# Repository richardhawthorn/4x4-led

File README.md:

### Features

- ESP8266 wifi processor
- 16 RGB Neopixels
- 2 x button inputs
- 3.3V operation
- Mini USB power connector
- FTDI programming port

### License

This work is licensed under a Creative Commons Attribution-ShareAlike 4.0 International License.

<br />
Designed by <a xmlns:cc="http://creativecommons.org/ns#" href="http://www.richardhawthorn.com" property="cc:attributionName" rel="cc:attributionURL" target="_blank">Richard Hawthorn</a><br />
<a rel="license" href="http://creativecommons.org/licenses/by-sa/4.0/" target="_blank">View License</a>

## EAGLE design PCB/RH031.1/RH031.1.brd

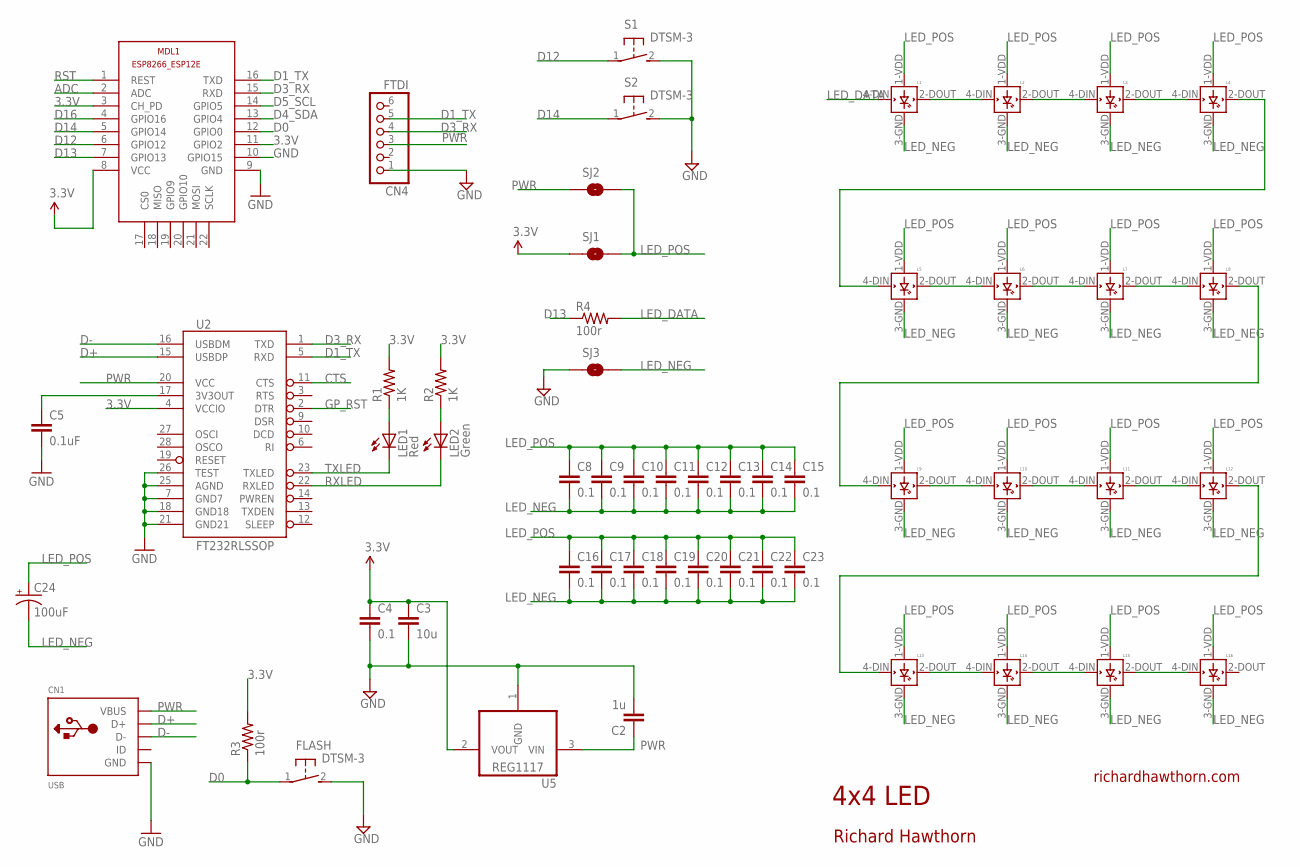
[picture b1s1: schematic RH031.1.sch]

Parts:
C2: 1u; 0603-CAP
C3: 10u; 0805-CAP
C4, C8, C9, C10, C11, C12, C13, C14, C15, C16, C17, C18, C19, C20, C21, C22, C23: 0.1; 0603-CAP
C5: 0.1uF; 0805
C24: 100uF; EIA7343
CN1: USB; USB-MINIB
CN4: FTDI; 1X06
FLASH: DTSM-3
L1, L2, L3, L4, L5, L6, L7, L8, L9, L10, L11, L12, L13, L14, L15, L16: WS2812B
LED1: Red; CHIPLED_0805
LED2: Green; CHIPLED_0805
MDL1: ESP8266-12EESP8266-ESP12E; ESP8266-ESP12E
R1, R2: 1K; 0805
R3, R4: 100r; 0603-RES
S1, S2: DTSM-3
SJ1, SJ2, SJ3: SOLDERJUMPERNO; SJ_2S-NO
U2: FT232RLSSOP; SSOP28DB
U5: REG1117; SOT223

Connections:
3.3V: C3.1, C4.1, MDL1.3 (CH_PD), MDL1.8 (VCC), MDL1.11 (GPIO2), R1.2, R2.2, R3.2, SJ1.1, U2.4 (VCCIO), U5.2 (VOUT)
3.3VOUT: C5.1, U2.17 (3V3OUT)
ADC: MDL1.2 (ADC)
CTS: U2.11 (CTS)
D0: FLASH.1, MDL1.12 (GPIO0), R3.1
D1_TX: CN4.5, MDL1.16 (TXD), U2.5 (RXD)
D3_RX: CN4.4, MDL1.15 (RXD), U2.1 (TXD)
D4_SDA: MDL1.13 (GPIO4)
D5_SCL: MDL1.14 (GPIO5)
D12: MDL1.6 (GPIO12), S1.1
D13: MDL1.7 (GPIO13), R4.1
D14: MDL1.5 (GPIO14), S2.1
D16: MDL1.4 (GPIO16)
D+: CN1.D+, U2.15 (USBDP)
D-: CN1.D-, U2.16 (USBDM)
GND: C2.2, C3.2, C4.2, C5.2, CN1.GND, CN4.1, FLASH.2, MDL1.9 (GND), MDL1.10 (GPIO15), S1.2, S2.2, SJ3.1, U2.7 (GND7), U2.18 (GND18), U2.21 (GND21), U2.25 (AGND), U2.26 (TEST), U5.1 (GND)
GP_RST: U2.2 (DTR)
LED-MID-1: L5.2-DOUT (DOUT), L6.4-DIN (DIN)
LED-MID-2: L7.2-DOUT (DOUT), L8.4-DIN (DIN)
LED-MID-3: L9.2-DOUT (DOUT), L10.4-DIN (DIN)
LED-OUT-1: L1.2-DOUT (DOUT), L2.4-DIN (DIN)
LED-OUT-2: L3.2-DOUT (DOUT), L4.4-DIN (DIN)
LED-OUT-3: L4.2-DOUT (DOUT), L5.4-DIN (DIN)
LED-OUT-4: L12.2-DOUT (DOUT), L13.4-DIN (DIN)
LED-OUT-5: L13.2-DOUT (DOUT), L14.4-DIN (DIN)
LED-OUT-6: L15.2-DOUT (DOUT), L16.4-DIN (DIN)
LED_DATA: L1.4-DIN (DIN), R4.2
LED_NEG: C8.2, C9.2, C10.2, C11.2, C12.2, C13.2, C14.2, C15.2, C16.2, C17.2, C18.2, C19.2, C20.2, C21.2, C22.2, C23.2, C24.C (-), L1.3-GND (GND), L2.3-GND (GND), L3.3-GND (GND), L4.3-GND (GND), L5.3-GND (GND), L6.3-GND (GND), L7.3-GND (GND), L8.3-GND (GND), L9.3-GND (GND), L10.3-GND (GND), L11.3-GND (GND), L12.3-GND (GND), L13.3-GND (GND), L14.3-GND (GND), L15.3-GND (GND), L16.3-GND (GND), SJ3.2
LED_POS: C8.1, C9.1, C10.1, C11.1, C12.1, C13.1, C14.1, C15.1, C16.1, C17.1, C18.1, C19.1, C20.1, C21.1, C22.1, C23.1, C24.A (+), L1.1-VDD (VDD), L2.1-VDD (VDD), L3.1-VDD (VDD), L4.1-VDD (VDD), L5.1-VDD (VDD), L6.1-VDD (VDD), L7.1-VDD (VDD), L8.1-VDD (VDD), L9.1-VDD (VDD), L10.1-VDD (VDD), L11.1-VDD (VDD), L12.1-VDD (VDD), L13.1-VDD (VDD), L14.1-VDD (VDD), L15.1-VDD (VDD), L16.1-VDD (VDD), SJ1.2, SJ2.2
unnamed: LED1.A, R1.1
unnamed: LED2.A, R2.1
unnamed: L2.2-DOUT (DOUT), L3.4-DIN (DIN)
unnamed: L6.2-DOUT (DOUT), L7.4-DIN (DIN)
unnamed: L8.2-DOUT (DOUT), L9.4-DIN (DIN)
unnamed: L10.2-DOUT (DOUT), L11.4-DIN (DIN)
unnamed: L11.2-DOUT (DOUT), L12.4-DIN (DIN)
unnamed: L14.2-DOUT (DOUT), L15.4-DIN (DIN)
PWR: C2.1, CN1.VBUS, CN4.3, SJ2.1, U2.20 (VCC), U5.3 (VIN)
RST: MDL1.1 (REST)
RXLED: LED2.C, U2.22 (RXLED)
TXLED: LED1.C, U2.23 (TXLED)

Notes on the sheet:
4x4 LED
richardhawthorn.com
Richard Hawthorn

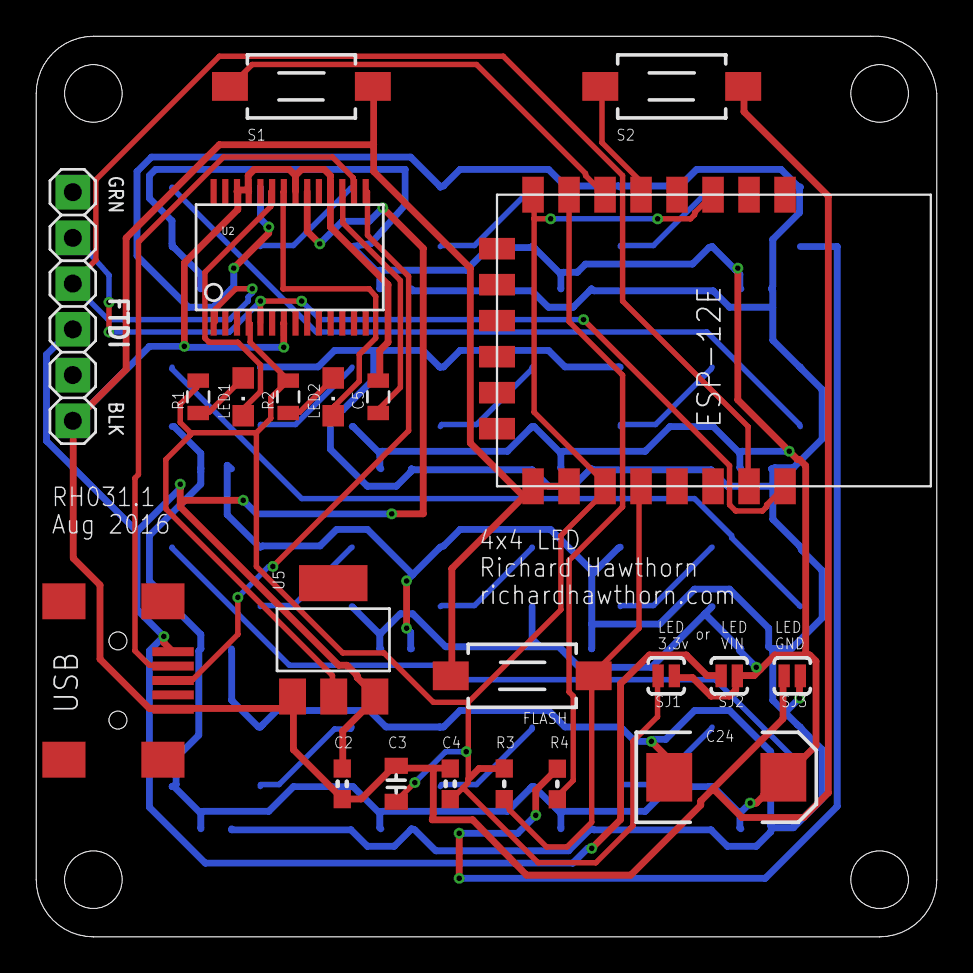
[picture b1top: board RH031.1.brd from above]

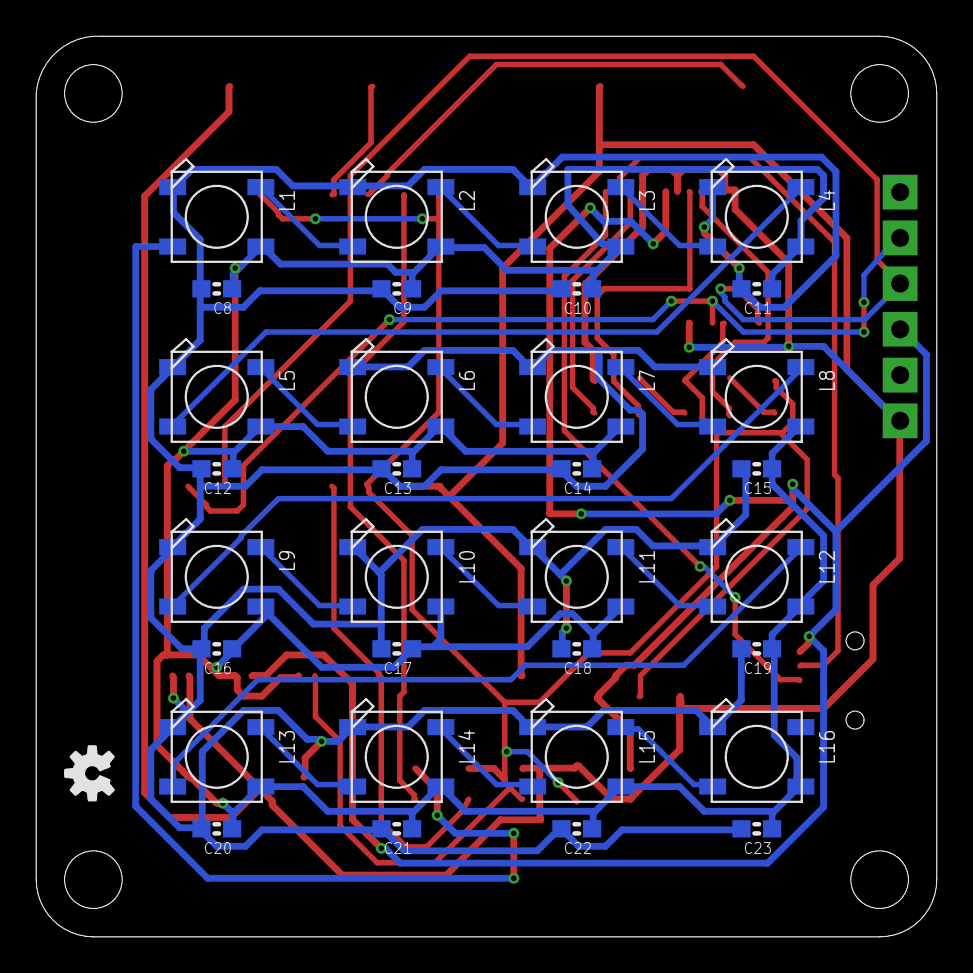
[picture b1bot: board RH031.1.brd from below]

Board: 2 copper layers, 50.0 x 50.0 mm, 55 parts (33 on the bottom side), 34 nets.

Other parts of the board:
U$3: OSHW-LOGO-S

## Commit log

2016-11-08 added design files
2016-11-08 add license
2018-01-29 add images

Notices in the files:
parts and their libraries:
SparkFun-Aesthetics: Licensing: CC v3.0 Share-Alike You are welcome to use this library for commercial purposes.
SparkFun-Retired: Licensing:Creative Commons ShareAlike 4.0 International - https://creativecommons.org/licenses/by-sa/4.0
